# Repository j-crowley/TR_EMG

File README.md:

# TR_EMG
The Trans-radial EMG (TREMG) is a PCB designed to increase SNR for surface-level EMG electrodes which is then digitized and sent to a controller to drive a robotic prosthetic. This is for individuals with upper limb amputations at the trans-radial level. It enables users to regain dexterity and perform a wide range of tasks using a prosthetic hand. This repository includes the final design of the PCB for this project and does not include the code.

# Credits
Credits to the rest of the capstone team, including: ThaneGallo and coop-bennett.

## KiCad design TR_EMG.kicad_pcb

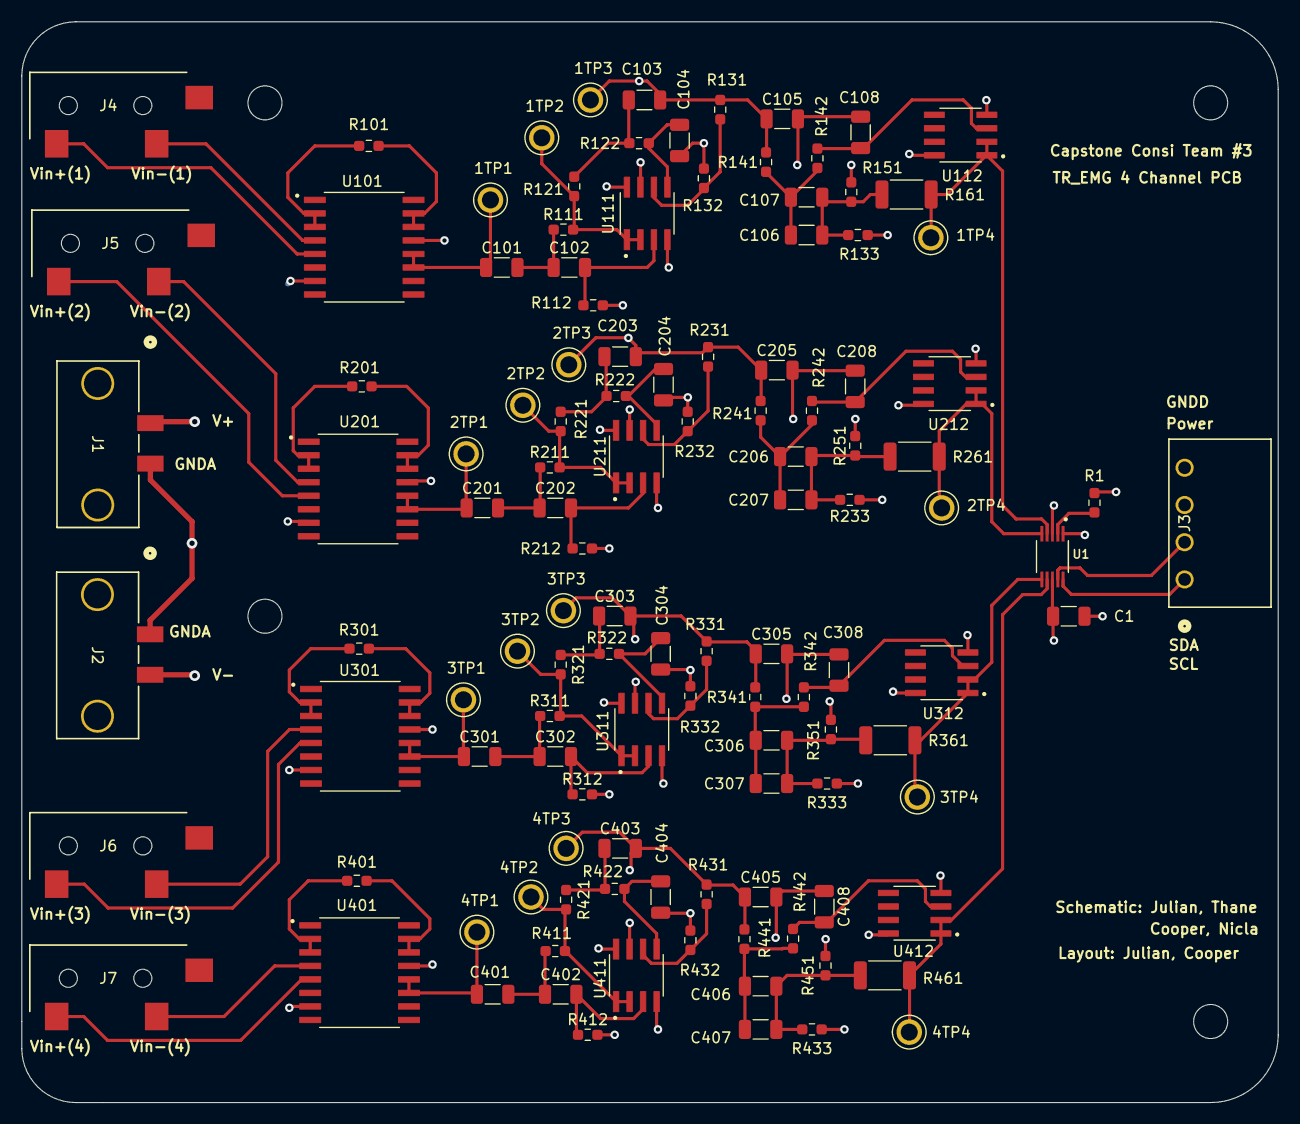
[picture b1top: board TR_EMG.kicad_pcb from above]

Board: 4 copper layers, 118.1 x 101.6 mm, 118 parts (0 on the bottom side), 76 nets.

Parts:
1TP1, 1TP2, 1TP3, 1TP4, 2TP1, 2TP2, 2TP3, 2TP4, 3TP1, 3TP2, 3TP3, 3TP4, 4TP1, 4TP2, 4TP3, 4TP4: 5012; TP_5012
C1: 0.1 u; C_1206_3216Metric
C101, C102, C103, C104, C105, C106, C107, C108, C201, C202, C203, C204, C205, C206, C207, C208, C301, C302, C303, C304, C305, C306, C307, C308, C401, C402, C403, C404, C405, C406, C407, C408: 0.1u; C_1206_3216Metric
J1, J2: 1727230; CONN_1727230_PXC
J3: 1844236; CONN_1844236_PXC
J4, J5, J6, J7: MJ-3523-SMT-TR; CONN_MJ-3523_CUD_CtYrd
R1, R131, R132, R231, R232, R331, R332, R431, R432: 1k; R_0603_1608Metric_Pad0.98x0.95mm_HandSolder
R101, R201, R301, R401: 100; R_0603_1608Metric_Pad0.98x0.95mm_HandSolder
R111, R112, R211, R212, R311, R312, R411, R412: 330k; R_0603_1608Metric_Pad0.98x0.95mm_HandSolder
R121, R122, R221, R222, R321, R322, R421, R422: 3.3k; R_0603_1608Metric_Pad0.98x0.95mm_HandSolder
R133, R233, R333, R433: 100k; R_0603_1608Metric_Pad0.98x0.95mm_HandSolder
R141, R142, R241, R242, R341, R342, R441, R442: 26.7k; R_0603_1608Metric_Pad0.98x0.95mm_HandSolder
R151, R251, R351, R451: 13k; R_0603_1608Metric_Pad0.98x0.95mm_HandSolder
R161, R261, R361, R461: 150; R_2010_5025Metric
U1: ADS1115IDGSR; ADS-SOP50P490X110-10N
U101, U201, U301, U401: INA115BU; INA-SOIC127P1030X265-16N
U111, U112, U211, U212, U311, U312, U411, U412: LT1169CS8-PBF; LT-SOIC127P599X175-8N

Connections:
/ADC/AIN0: 1TP4.TP, R161.2, U1.4 (AIN0), U112.1 (OUTA), U112.2 (-INA)
/ADC/AIN1: 2TP4.TP, R261.2, U1.5 (AIN1), U212.1 (OUTA), U212.2 (-INA)
/ADC/AIN2: 3TP4.TP, R361.2, U1.6 (AIN2), U312.1 (OUTA), U312.2 (-INA)
/ADC/AIN3: 4TP4.TP, R461.2, U1.7 (AIN3), U412.1 (OUTA), U412.2 (-INA)
/ADC/Power: C1.2, J3.3, R1.1, U1.8 (VDD)
/ADC/SCL: J3.1, U1.10 (SCL)
/ADC/SDA: J3.2, U1.9 (SDA)
/Filter1/2nd Band Pass Filter (5 - 500 Hz)/Vin: 1TP1.TP, C101.1, U101.11 (VO), U101.12 (FB)
/Filter1/2nd Band Pass Filter (5 - 500 Hz)/Vout: 1TP3.TP, C103.2, C105.1, R131.2, R141.1, U111.7 (OUTB)
/Filter2/2nd Band Pass Filter (5 - 500 Hz)/Vin: 2TP1.TP, C201.1, U201.11 (VO), U201.12 (FB)
/Filter2/2nd Band Pass Filter (5 - 500 Hz)/Vout: 2TP3.TP, C203.2, C205.1, R231.2, R241.1, U211.7 (OUTB)
/Filter3/2nd Band Pass Filter (5 - 500 Hz)/Vin: 3TP1.TP, C301.1, U301.11 (VO), U301.12 (FB)
/Filter3/2nd Band Pass Filter (5 - 500 Hz)/Vout: 3TP3.TP, C303.2, C305.1, R331.2, R341.1, U311.7 (OUTB)
/Filter4/2nd Band Pass Filter (5 - 500 Hz)/Vin: 4TP1.TP, C401.1, U401.11 (VO), U401.12 (FB)
/Filter4/2nd Band Pass Filter (5 - 500 Hz)/Vout: 4TP3.TP, C403.2, C405.1, R431.2, R441.1, U411.7 (OUTB)
GNDA: C104.2, C204.2, C304.2, C404.2, J1.2, J2.1, R112.2, R132.2, R133.1, R212.2, R232.2, R233.1, R312.2, R332.2, R333.1, R412.2, R432.2, R433.1
GNDD: C1.1, J3.4, U1.1 (ADDR), U1.3 (GND)
unnamed: C101.2, C102.1, R111.1
unnamed: C103.1, R121.1, R122.1
unnamed: C105.2, C108.1, R151.2
unnamed: C106.1, C107.1, R133.2, R151.1, R161.1
unnamed: C106.2, C107.2, R141.2, R142.1
unnamed: C201.2, C202.1, R211.1
unnamed: C203.1, R221.1, R222.1
unnamed: C205.2, C208.1, R251.2
unnamed: C206.1, C207.1, R233.2, R251.1, R261.1
unnamed: C206.2, C207.2, R241.2, R242.1
unnamed: C301.2, C302.1, R311.1
unnamed: C303.1, R321.1, R322.1
unnamed: C305.2, C308.1, R351.2
unnamed: C306.1, C307.1, R333.2, R351.1, R361.1
unnamed: C306.2, C307.2, R341.2, R342.1
unnamed: C401.2, C402.1, R411.1
unnamed: C403.1, R421.1, R422.1
unnamed: C405.2, C408.1, R451.2
unnamed: C406.1, C407.1, R433.2, R451.1, R461.1
unnamed: C406.2, C407.2, R441.2, R442.1
unnamed: R1.2, U1.2 (ALERT/RDY)
unnamed: R101.1, U101.2 (G_SEN1), U101.3 (RG)
unnamed: R101.2, U101.14 (RG__1), U101.15 (G_SEN2)
unnamed: C102.2, R112.1, U111.3 (+INA)
unnamed: C104.1, R122.2, U111.5 (+INB)
unnamed: 1TP2.TP, R111.2, R121.2, U111.1 (OUTA), U111.2 (-INA)
unnamed: R131.1, R132.1, U111.6 (-INB)
unnamed: C108.2, R142.2, U112.3 (+INA)
unnamed: R201.1, U201.2 (G_SEN1), U201.3 (RG)
unnamed: R201.2, U201.14 (RG__1), U201.15 (G_SEN2)
unnamed: C202.2, R212.1, U211.3 (+INA)
unnamed: C204.1, R222.2, U211.5 (+INB)
unnamed: 2TP2.TP, R211.2, R221.2, U211.1 (OUTA), U211.2 (-INA)
unnamed: R231.1, R232.1, U211.6 (-INB)
unnamed: C208.2, R242.2, U212.3 (+INA)
unnamed: R301.1, U301.2 (G_SEN1), U301.3 (RG)
unnamed: R301.2, U301.14 (RG__1), U301.15 (G_SEN2)
unnamed: C302.2, R312.1, U311.3 (+INA)
unnamed: C304.1, R322.2, U311.5 (+INB)
unnamed: 3TP2.TP, R311.2, R321.2, U311.1 (OUTA), U311.2 (-INA)
unnamed: R331.1, R332.1, U311.6 (-INB)
unnamed: C308.2, R342.2, U312.3 (+INA)
unnamed: R401.1, U401.2 (G_SEN1), U401.3 (RG)
unnamed: R401.2, U401.14 (RG__1), U401.15 (G_SEN2)
unnamed: C402.2, R412.1, U411.3 (+INA)
unnamed: C404.1, R422.2, U411.5 (+INB)
unnamed: 4TP2.TP, R411.2, R421.2, U411.1 (OUTA), U411.2 (-INA)
unnamed: R431.1, R432.1, U411.6 (-INB)
unnamed: C408.2, R442.2, U412.3 (+INA)
V+: J1.1, U101.13 (V+), U111.8 (V+), U112.8 (V+), U201.13 (V+), U211.8 (V+), U212.8 (V+), U301.13 (V+), U311.8 (V+), U312.8 (V+), U401.13 (V+), U411.8 (V+), U412.8 (V+)
V-: J2.2, U101.7 (V-), U111.4 (V-), U112.4 (V-), U201.7 (V-), U211.4 (V-), U212.4 (V-), U301.7 (V-), U311.4 (V-), U312.4 (V-), U401.7 (V-), U411.4 (V-), U412.4 (V-)
Vin+(1): J4.1, U101.5 (VIN+)
Vin+(2): J5.1, U201.5 (VIN+)
Vin+(3): J6.1, U301.5 (VIN+)
Vin+(4): J7.1, U401.5 (VIN+)
Vin-(1): J4.2, U101.4 (VIN-)
Vin-(2): J5.2, U201.4 (VIN-)
Vin-(3): J6.2, U301.4 (VIN-)
Vin-(4): J7.2, U401.4 (VIN-)

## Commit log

2024-01-23 Backlink to CADLAB.io has been added.
2024-01-23 Create dir
2024-01-23 add board, schematic, and project file
2024-01-23 create symbol dir #1
2024-01-23 Create footprint dir #1
2024-01-23 Create footprint dir
2024-01-23 Rename READ_ME.md to README.md
2024-01-23 added 2 op amp chip symbols and footprint #1
2024-01-23 added instrumentation amplifier #1
2024-01-24 begin TR_EMGkicad
2024-01-24 add schematic
2024-01-25 Added Hierarchy to initial design
    Added hierarchy for the 2nd order lowpass and the band stop filter
2024-01-26 add more hierarchical sheets for better formating (instru. amp. and HPF)
2024-01-27 band pass and hierarchy update
    merged high pass and low pass and edited the hierarchy accoridngly
2024-01-29 ltspice sims for BPF, BSF, and all filters total
2024-01-30 redone notch filter and minor tweaks to bandpass filter
2024-01-31 added new filter sims, and tweaked components for notch and bandpass filter and circuits for both as well
2024-02-01 add ADC block
2024-02-01 excess files
2024-02-01 symbol library + file
2024-02-03 swapped lpf and hpf in bandpass filter and added testpoints on various filter circuits
2024-02-06 Filter abstraction and Input output connectors
    Abstracted filters so there are 4 signal paths to go to ADC. Added input and output connectors.
2024-02-06 added connectors for electrode inputs and revamped battery connectors
2024-02-06 removed sda scl pullups, removed electrode connectors to make space for proper connectors later
2024-02-07 added audio jack connectors for emg connections
2024-02-07 Reference Designator and Footprint Updates
    Changed almost all reference designators to group similar components by what filter they are a part of and what value they have.
    Need to:
    - Sort symbol data for ADC and OpAmps to correct folders
    - get footprint files for ADC and OpAmps
2024-02-07 updated GND symbols for appropriate seperatiion of analog and digital grounds
2024-02-07 renamed and relinked footprints with better clarity footprint file names
2024-02-08 final adjustments for power constraints with changed footprint and resistor values on notch filter feedback portion
2024-02-08 changed capacitor footprint to match in stock components (0603 to 1206)
2024-02-08 first chunk of pcb layout and schematics mods (no connects on pins and changing global labels to hieracarchical labels), one filtering pcb circuit layed out
2024-02-08 finished majority of layout, pcb expanded to four copper layers to accomadate power planes
2024-02-08 Final touches to silkscreen on pcb, DRC check still needed
2024-02-08 modified footprints and IC silkscreen refereence designators to comply with DRC checks
2024-02-08 DRC check passed, but ADC/ADS footprint needs to be checked for JLCPCB compatability (pads may be too close together)
2024-02-08 Extended ground planes, rerouted some traces into vias. and pushed connectors to edge of board
2024-02-08 ToTheEdge,LCSCNums
    Moved the 3.5mm connectors to the edge and edited their footprint courtyard so no errors. Adjusted the planes so that it bordered 3.5mm connector pads well and didn't go to edge cuts. Added LCSC part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
2024-02-08 Pushed adc connector to edge of pcb
2024-02-09 nore footprint tweaking to meet DRC requirements
2024-02-09 added mounting holes, board ready for export
